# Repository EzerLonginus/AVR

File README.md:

# AVR
Experiments in AVR programming

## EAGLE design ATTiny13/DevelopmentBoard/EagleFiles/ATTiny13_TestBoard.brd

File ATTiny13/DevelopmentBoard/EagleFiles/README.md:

# ATTiny13 Development Board
Eagle Files ATTiny13A Development board.  Designed for Bantam CNC using single sided board with 1/64" bit for traces and 1/32" bit for holes and outline.

## Schematic

## Layout

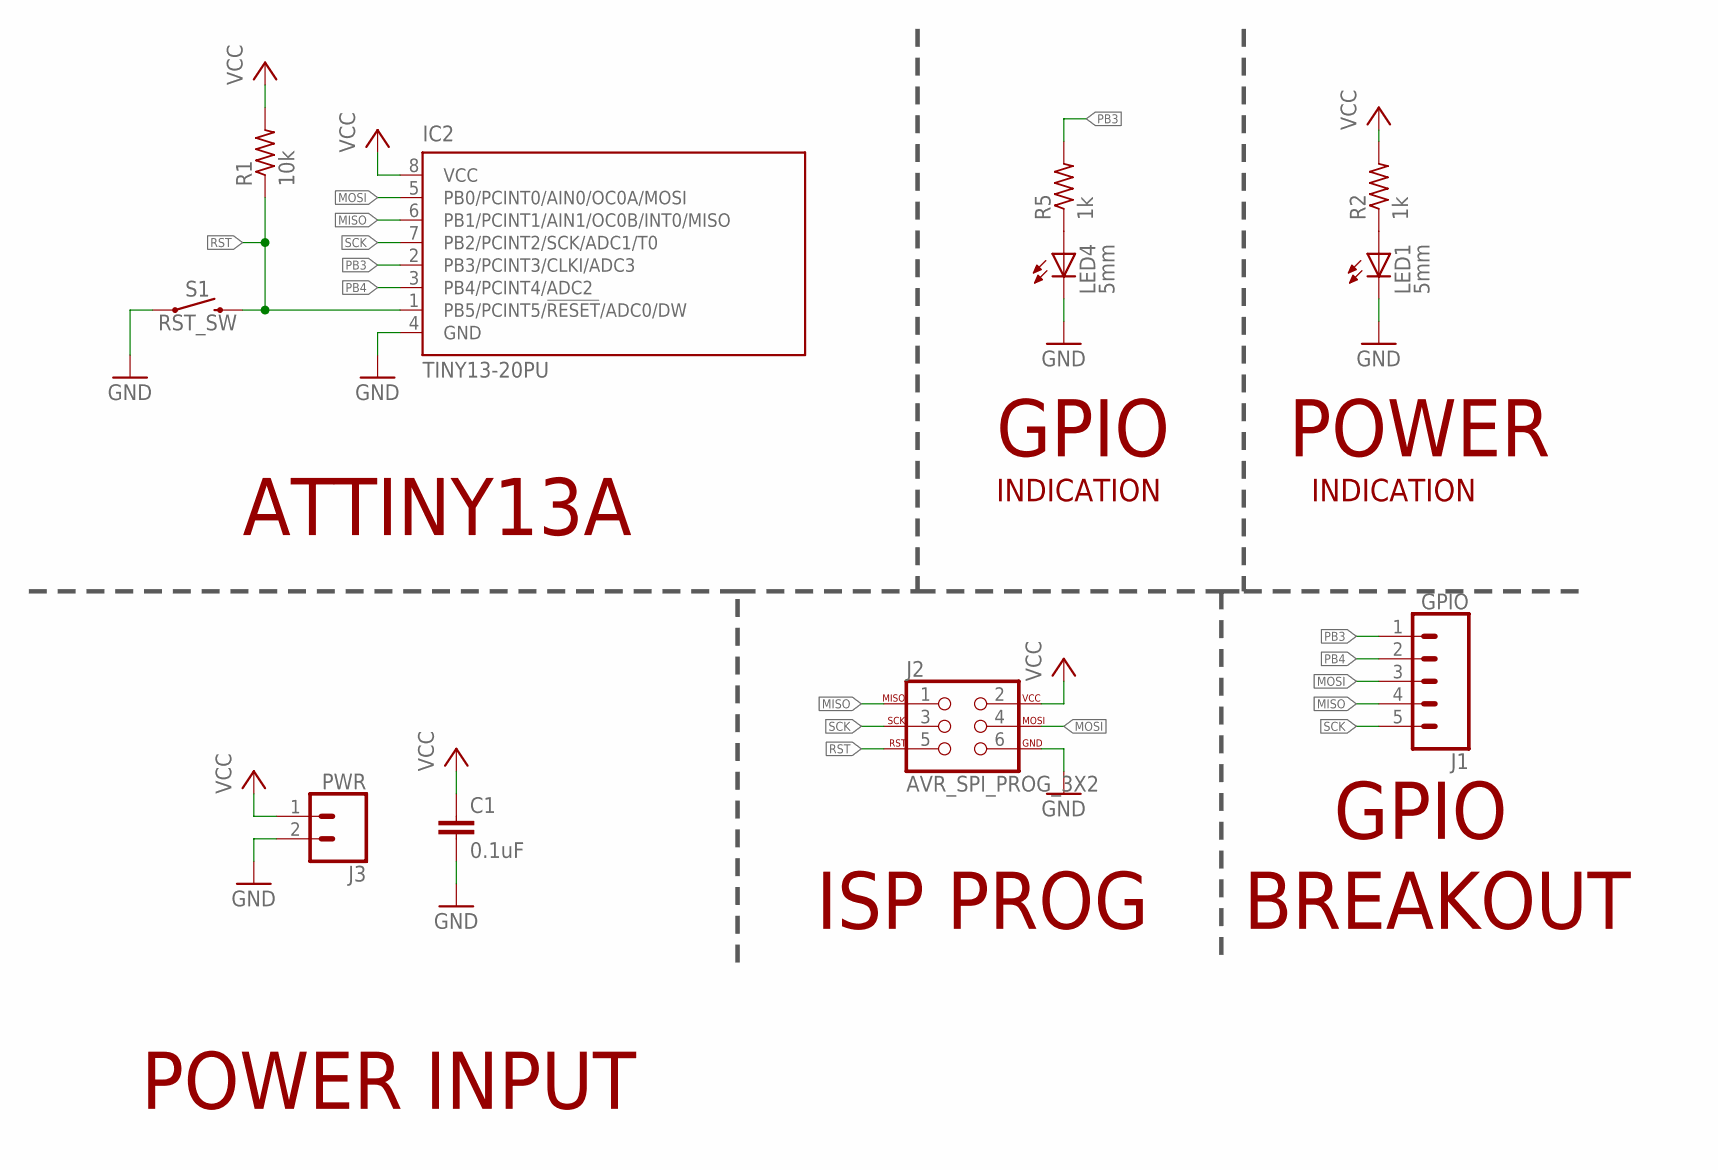
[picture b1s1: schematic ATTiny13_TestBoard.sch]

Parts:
C1: 0.1uF; C050-025X075
IC2: TINY13-20PU; DIL08
J1: GPIO; SCREWTERMINAL-3.5MM-5
J2: AVR_SPI_PROG_3X2; 2X3-NS
J3: PWR; SCREWTERMINAL-3.5MM-2-NS
LED1, LED4: 5mm; LED5MM
R1: 10k; 0204/7
R2, R5: 1k; 0204/7
S1: RST_SW; TACTILE_SWITCH_PTH_6.0MM

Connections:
GND: C1.2, IC2.4 (GND), J2.6, J3.2, LED1.K (C), LED4.K (C), S1.1
MISO: IC2.6 (PB1/PCINT1/AIN1/OC0B/INT0/MISO), J1.4, J2.1
MOSI: IC2.5 (PB0/PCINT0/AIN0/OC0A/MOSI), J1.3, J2.4
unnamed: LED1.A, R2.1
unnamed: LED4.A, R5.1
PB3: IC2.2 (PB3/PCINT3/CLKI/ADC3), J1.1, R5.2
PB4: IC2.3 (PB4/PCINT4/ADC2), J1.2
RST: IC2.1 (PB5/PCINT5/!RESET!/ADC0/DW), J2.5, R1.1, S1.3 (2)
SCK: IC2.7 (PB2/PCINT2/SCK/ADC1/T0), J1.5, J2.3
VCC: C1.1, IC2.8 (VCC), J2.2, J3.1, R1.2, R2.2

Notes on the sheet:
ATTINY13A
ISP PROG
GPIO
BREAKOUT
POWER INPUT
INDICATION
POWER

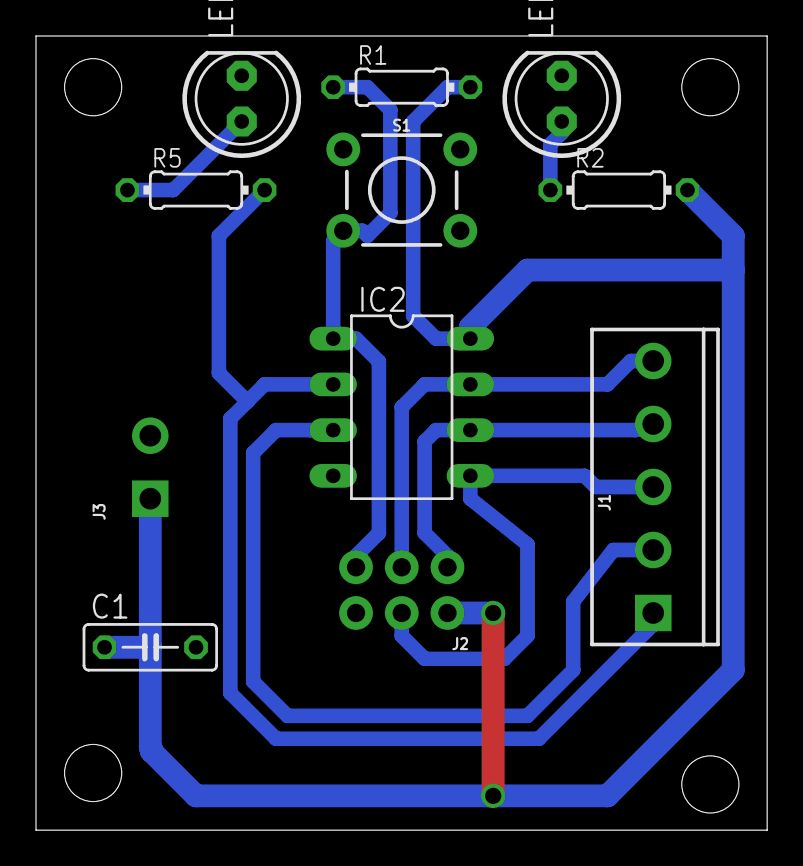
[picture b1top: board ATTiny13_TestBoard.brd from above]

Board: 2 copper layers, 40.6 x 44.1 mm, 11 parts (0 on the bottom side), 10 nets.

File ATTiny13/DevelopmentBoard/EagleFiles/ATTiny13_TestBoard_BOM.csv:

"Qty";"Value";"Device";"Package";"Parts";"Description";"MF";"MPN";"OC_FARNELL";"OC_NEWARK";"PROD_ID";"SF_SKU";"SPICEPREFIX";
"1";"0.1uF";"C-EU050-025X075";"C050-025X075";"C1";"CAPACITOR, European symbol";"";"";"";"";"";"";"C";
"1";"10k";"R-US_0204/7";"0204/7";"R1";"RESISTOR, American symbol";"";"";"";"";"";"";"R";
"2";"1k";"R-US_0204/7";"0204/7";"R2, R5";"RESISTOR, American symbol";"";"";"";"";"";"";"R";
"2";"5mm";"LED5MM";"LED5MM";"LED1, LED4";"LED";"";"";"";"";"";"";"";
"1";"AVR_SPI_PROG_3X2";"AVR_SPI_PROG_3X2NS";"2X3-NS";"J2";"AVR ISP 6 Pin";"";"";"";"";"";"";"";
"1";"GPIO";"CONN_05SCREW";"SCREWTERMINAL-3.5MM-5";"J1";"Multi connection point. Often used as Generic Header-pin footprint for 0.1 inch spaced/style header connections";"";"";"";"";"Combine 8288+8399";"";"";
"1";"PWR";"CONN_023.5MM-NO_SILK";"SCREWTERMINAL-3.5MM-2-NS";"J3";"Multi connection point. Often used as Generic Header-pin footprint for 0.1 inch spaced/style header connections";"";"";"";"";"CONN-08399";"";"";
"1";"RST_SW";"MOMENTARY-SWITCH-SPST-PTH-6.0MM";"TACTILE_SWITCH_PTH_6.0MM";"S1";"Momentary Switch (Pushbutton) - SPST";"";"";"";"";" SWCH-08441";"COM-00097";"";
"1";"TINY13-20PU";"TINY13-20PU";"DIL08";"IC2";"8-bit AVR Microcontroller with 1K Bytes In-System Programmable Flash";"";"ATTINY13-20PU";"9171550";"96K6521";"";"";"";

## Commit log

2020-04-27 Initial Commit
    Basic Development Board and Assembly Code for the ATTiny13A
2020-04-27 Assembly Include Files and Delay
    Adding addtional Assembly files to existing project. Using hardcoded subroutine delays
2020-04-27 DevelopmentBoardImages
    Updated Images of the Development board. Updated ReadMes
2020-04-27 ReadMe Fix
    Fixing Image Link on ReadMes
2020-04-27 ReadMe Title Fix
    Fixing Titles on ReadMes
2020-05-08 UART TX Code
    Adding code to allow for serial transmission on the ATTiny13A at 115200 and 57600 baud rates.

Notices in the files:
parts and their libraries:
SparkFun-Connectors: Licensing: Creative Commons ShareAlike 4.0 International - https://creativecommons.org/licenses/by-sa/4.0
